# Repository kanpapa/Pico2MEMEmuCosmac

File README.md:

# Pico2MEMEmuCOSMAC

このリポジトリはkyo-ta04(DragonballEZ)さんの[Pico2ROMEmuBR](https://github.com/kyo-ta04/Pico2ROMEmuBR)のコードを応用して、COSMAC（CDP1802）のROM/RAMエミュレータとして動かしてみた実験的なプロジェクトです。

## 概要
- COSMAC CPUの動作クロックは1.79MHzです。
- ROM/RAMは各32KBを割り当てて確認しましたが、64KBのアドレス空間内であればカスタマイズ可能です。
- ROMにはテストプログラムとしてQ出力のLチカを組み込んでいます。rom_const.cのコメントを参照してください。
- 専用基板Rev.0.1にはSBC1802にあるインジケーターをオプション回路として追加しています。

詳細はソースをご確認ください。

## 回路図
- ブレッドボード版回路図

- 専用基板Rev.0.1 回路図

[PDF](/IMG/Pico2MEMEmuCosmac_sch_rev01.pdf)

## PCB
- [KiCADデータ](/kicad)
- [Gerberデータ](/kicad/gerber/)
- PCB 3Dイメージ

## BOM
|Item|Qty|Reference(s)|Value|Description|Datasheet|
| --- | --- | --- | --- | --- | --- |
|1|1|A1|RaspberryPi_Pico2|Raspberry Pi Pico 2|https://akizukidenshi.com/catalog/g/g129604/|
|2|1|U1|CDP1802ACE|CDP1802ACE microprocessor|http://www.cosmacelf.com/publications/data-sheets/cdp1802.pdf|
|3|1|C1|0.1uF|リード型積層セラミックコンデンサー 0.1μF50V F 2.54mm|https://akizukidenshi.com/catalog/g/g100090/|
|4|1|D1|1N4148|汎用小信号高速スイッチング・ダイオード 1N4148 100V200mA|https://akizukidenshi.com/catalog/g/g100941/|
|5|1|R1|100|カーボン抵抗(炭素皮膜抵抗) 1/6W100Ω|https://akizukidenshi.com/catalog/g/g116101/|
|6|2|RN1,RN2|10K|集合抵抗 4素子 10kΩ|https://akizukidenshi.com/catalog/g/g111909/|
|7|1|SW1|RUN|タクトスイッチ(水色)|https://akizukidenshi.com/catalog/g/g103649/|
|8|1|U1 socket||丸ピンICソケット (40P)|https://akizukidenshi.com/catalog/g/g100034/|
|9※|1|J1|Conn_01x06|ピンヘッダー (L型) 1×6 (6P)|https://akizukidenshi.com/catalog/g/g105336/|
|10※|1|U2|74HC04|6回路入インバーター TC74HC04AF|https://akizukidenshi.com/catalog/g/g111490/|
|11※|5|D2,D3,D4,D5,D6|LED|緑色チップLED 1608 OSG50603C1E|https://akizukidenshi.com/catalog/g/g108275/|
|12※|5|R2,R3,R4,R5,R6|1k|チップ抵抗 1608 1/8W1kΩ|https://akizukidenshi.com/catalog/g/g130351/|

※9～12はオプションです。

## マニュアル
- [Visual Studio Code での Raspberry Pi Pico プロジェクトのビルド方法](/docs/raspberry-pi-pico-vscode-build.md)
- [Lチカの楽しみかた](/docs/blink.md)
- [RCA BASIC3の楽しみかた](/docs/MCBASIC3.md)
- [MCSMP Super Monitor+BASIC3の楽しみかた](/docs/MCSMP20A.md)

## 資料
- ブレッドボードで実験中の様子

- 専用基板に実装した状態

- 専用基板で動作中の様子

## ライセンス
本プロジェクトのソースコードは[Pico2ROMEmuBR](https://github.com/kyo-ta04/Pico2ROMEmuBR)のライセンスに従います。

## 免責事項
本ソフトウェアは現状のまま提供されます。いかなる損害についても作者は責任を負いません。

## 謝辞
kyo-ta04(DragonballEZ)さんをはじめとするPico2ROMEmuプロジェクトに関わる全ての方々

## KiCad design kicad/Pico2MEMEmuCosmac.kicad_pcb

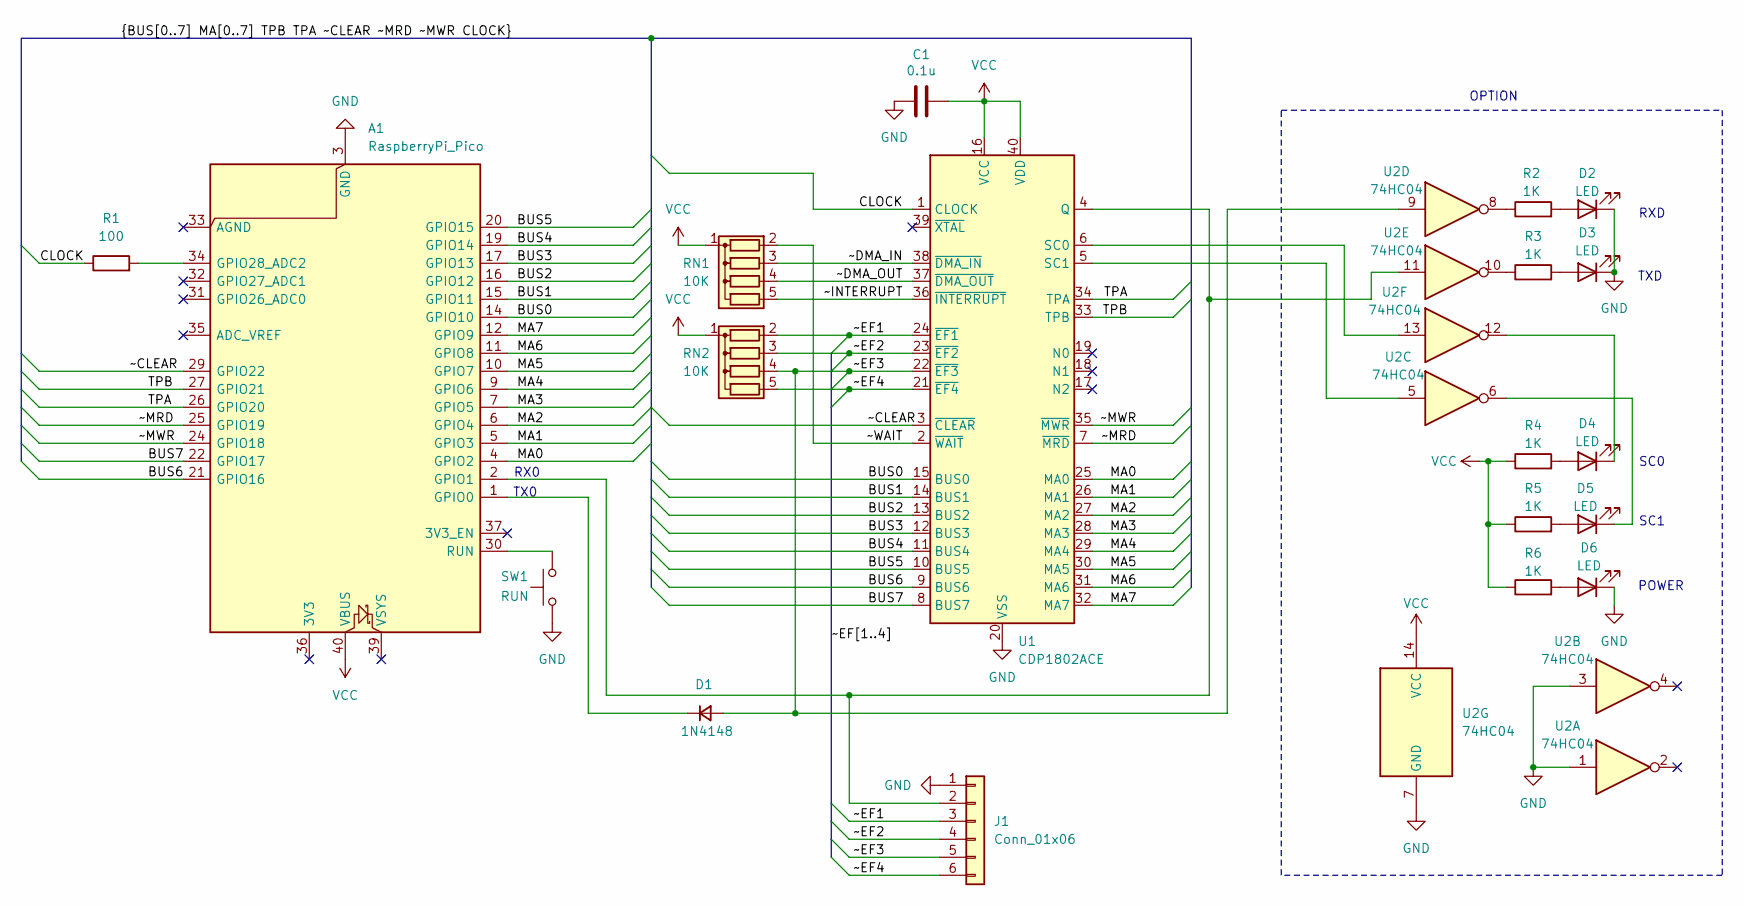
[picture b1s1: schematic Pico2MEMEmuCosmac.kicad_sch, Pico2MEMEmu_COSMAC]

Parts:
A1: RaspberryPi_Pico; RaspberryPi_Pico_Common_Unspecified
C1: 0.1u; C_Disc_D3.0mm_W1.6mm_P2.50mm
D1: 1N4148; D_DO-35_SOD27_P2.54mm_Vertical_KathodeUp
D2, D3, D4, D5, D6: LED; LED_0603_1608Metric
J1: Conn_01x06; PinHeader_1x06_P2.54mm_Vertical
R1: 100; R_Axial_DIN0204_L3.6mm_D1.6mm_P5.08mm_Horizontal
R2, R3, R4, R5, R6: 1K; R_0603_1608Metric
RN1, RN2: 10K; R_Array_SIP5
SW1: RUN; SW_PUSH_6mm
U1: CDP1802ACE; DIP-40_W15.24mm_Socket_LongPads
U2: 74HC04; SO-14_5.3x10.2mm_P1.27mm

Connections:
/BUS0: A1.14 (GPIO10), U1.15 (BUS0)
/BUS1: A1.15 (GPIO11), U1.14 (BUS1)
/BUS2: A1.16 (GPIO12), U1.13 (BUS2)
/BUS3: A1.17 (GPIO13), U1.12 (BUS3)
/BUS4: A1.19 (GPIO14), U1.11 (BUS4)
/BUS5: A1.20 (GPIO15), U1.10 (BUS5)
/BUS6: A1.21 (GPIO16), U1.9 (BUS6)
/BUS7: A1.22 (GPIO17), U1.8 (BUS7)
/CLOCK: R1.1, U1.1 (CLOCK)
/MA0: A1.4 (GPIO2), U1.25 (MA0)
/MA1: A1.5 (GPIO3), U1.26 (MA1)
/MA2: A1.6 (GPIO4), U1.27 (MA2)
/MA3: A1.7 (GPIO5), U1.28 (MA3)
/MA4: A1.9 (GPIO6), U1.29 (MA4)
/MA5: A1.10 (GPIO7), U1.30 (MA5)
/MA6: A1.11 (GPIO8), U1.31 (MA6)
/MA7: A1.12 (GPIO9), U1.32 (MA7)
/TPA: A1.26 (GPIO20), U1.34 (TPA)
/TPB: A1.27 (GPIO21), U1.33 (TPB)
/~CLEAR: A1.29 (GPIO22), U1.3 (~CLEAR)
/~DMA_IN: RN1.3 (R2), U1.38 (~DMA_IN)
/~DMA_OUT: RN1.4 (R3), U1.37 (~DMA_OUT)
/~EF1: J1.3, RN2.2 (R1), U1.24 (~EF1)
/~EF2: J1.4, RN2.3 (R2), U1.23 (~EF2)
/~EF3: D1.2 (A), J1.5, RN2.4 (R3), U1.22 (~EF3), U2.9
/~EF4: J1.6, RN2.5 (R4), U1.21 (~EF4)
/~INTERRUPT: RN1.5 (R4), U1.36 (~INTERRUPT)
/~MRD: A1.25 (GPIO19), U1.7 (~MRD)
/~MWR: A1.24 (GPIO18), U1.35 (~MWR)
/~WAIT: RN1.2 (R1), U1.2 (~WAIT)
GND: A1.3 (GND), A1.8 (GND), A1.13 (GND), A1.18 (GND), A1.23 (GND), A1.28 (GND), A1.38 (GND), C1.2, D2.1 (K), D3.1 (K), D6.1 (K), J1.1, SW1.2, U1.20 (VSS), U2.1, U2.3, U2.7 (GND)
unnamed: A1.1 (GPIO0), D1.1 (K)
unnamed: A1.2 (GPIO1), J1.2, U1.4 (Q), U2.11
unnamed: A1.34 (GPIO28_ADC2), R1.2
unnamed: A1.30 (RUN), SW1.1
unnamed: D2.2 (A), R2.2
unnamed: D3.2 (A), R3.2
unnamed: D4.2 (A), R4.2
unnamed: D4.1 (K), U2.12
unnamed: D5.2 (A), R5.2
unnamed: D5.1 (K), U2.6
unnamed: D6.2 (A), R6.2
unnamed: R2.1, U2.8
unnamed: R3.1, U2.10
unnamed: U1.6 (SC0), U2.13
unnamed: U1.5 (SC1), U2.5
VCC: A1.40 (VBUS), C1.1, R4.1, R5.1, R6.1, RN1.1 (common), RN2.1 (common), U1.16 (VCC), U1.40 (VDD), U2.14 (VCC)

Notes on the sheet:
SC1
RX0
TXD
TX0
OPTION
POWER
RXD
SC0

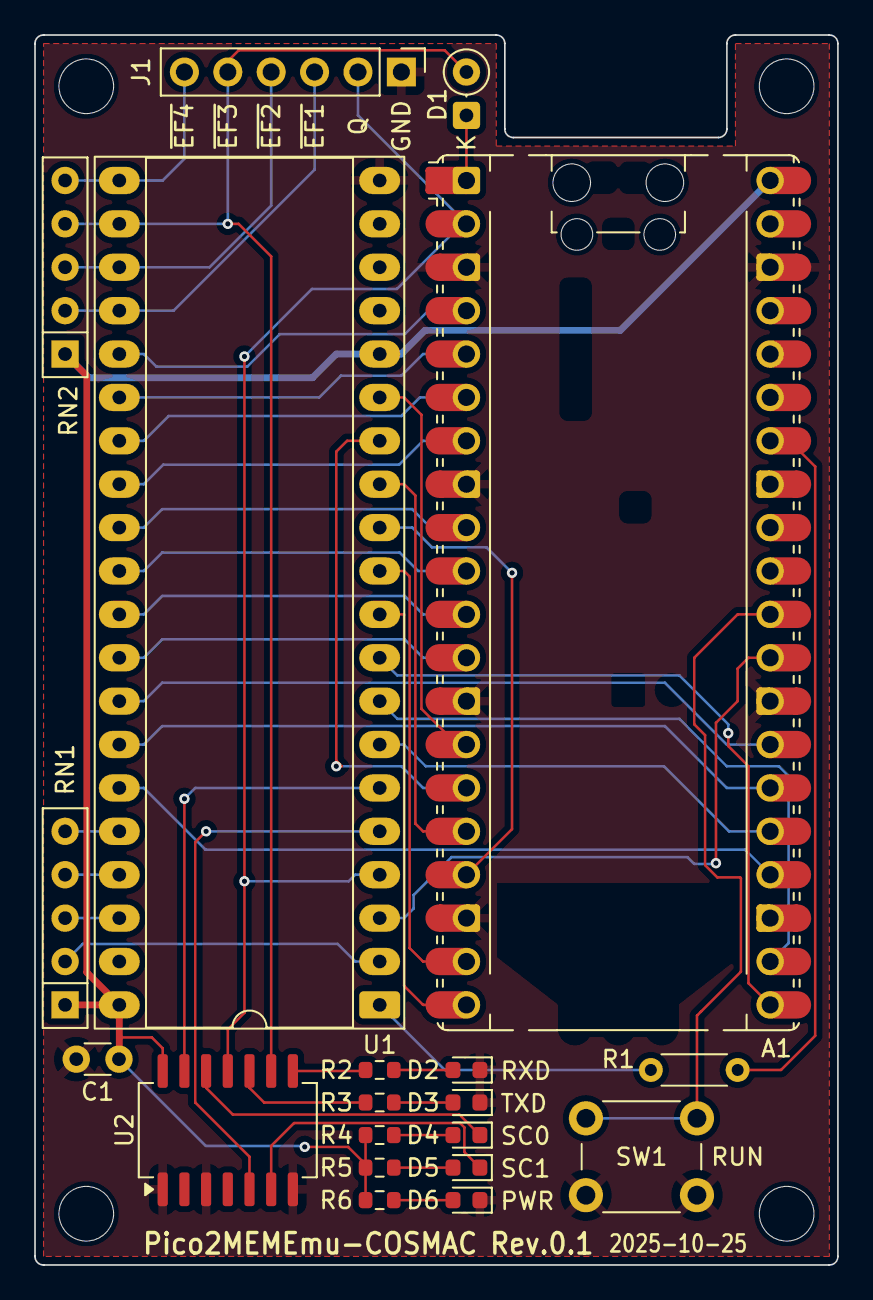
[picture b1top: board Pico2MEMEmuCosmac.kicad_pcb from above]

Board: 2 copper layers, 47.0 x 72.0 mm, 24 parts (0 on the bottom side), 47 nets.

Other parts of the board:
MH1, MH2, MH3, MH4: MountingHole_3.2mm_M3

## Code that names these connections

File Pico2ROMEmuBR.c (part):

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
#define DATA_PINS_BASE 10  // GP10～GP17 (D0-D7 8bit)
#define ADDR_PINS_BASE 2   // GP2～GP9 (MA0-MA7 8bit)
#define MWR_PIN 18
#define MRD_PIN 19
#define TPA_PIN 20
#define TPB_PIN 21
#define RESETOUT_PIN 22     // GP22 (リセット出力)
#define CLKOUT_PIN 28       // GP28 (クロック出力)

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
    // UART0の初期化
    uart_init(UART_ID, BAUD_RATE);
    // UARTピンの設定（GPIO0=TX, GPIO1=RX）
    gpio_set_function(UART_TX_PIN, GPIO_FUNC_UART);
    gpio_set_function(UART_RX_PIN, GPIO_FUNC_UART);

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    pio_sm_config c_addr = cdp1802_get_address_program_get_default_config(offset_addr);
    sm_config_set_in_pins(&c_addr, ADDR_PINS_BASE);
    sm_config_set_out_pins(&c_addr, DATA_PINS_BASE, 8);
    sm_config_set_jmp_pin(&c_addr, MRD_PIN); // MRDをJMPピンとして設定
    // PIOが制御するピンの方向を設定
    pio_sm_set_consecutive_pindirs(pio, sm_addr, ADDR_PINS_BASE, 8, false); // ADDRESSバスは入力
    pio_sm_set_consecutive_pindirs(pio, sm_addr, TPA_PIN, 1, false);  // TPAは入力
    pio_sm_set_consecutive_pindirs(pio, sm_addr, TPB_PIN, 1, false);  // TPBは入力
    pio_sm_set_consecutive_pindirs(pio, sm_addr, DATA_PINS_BASE, 8, false); // 初期は入力
    pio_sm_set_consecutive_pindirs(pio, sm_addr, MRD_PIN, 1, false);  // MRDは入力
    
    // 1. 書き込み用SM (sm_write)
    pio_sm_config c_write = cdp1802_write_mem_program_get_default_config(offset_write);
    sm_config_set_in_pins(&c_write, DATA_PINS_BASE); // DATAバスは入力
    // PIOが制御するピンの方向を設定
    pio_sm_set_consecutive_pindirs(pio, sm_write, MWR_PIN, 1, false); // MWR_PINは入力
    pio_sm_set_consecutive_pindirs(pio, sm_write, DATA_PINS_BASE, 8, false); // DATAバスは入力

    // 2. CPUクロック生成用SM (sm_clock)
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    }
    
    pio_gpio_init(pio, RESETOUT_PIN); // リセット出力ピン(GP25)の初期化
    pio_gpio_init(pio, MRD_PIN); // MRDピン(GP18)の初期化
    pio_gpio_init(pio, MWR_PIN); // MWRピン(GP19)の初期化
    pio_gpio_init(pio, TPA_PIN); // TPAピン(GP20)の初期化
    pio_gpio_init(pio, TPB_PIN); // TPBピン(GP21)の初期化
    pio_gpio_init(pio, CLKOUT_PIN); // CLK出力ピン(GP28)の初期化

    // Pullup
    gpio_set_pulls(MRD_PIN, true, false);
    gpio_set_pulls(MWR_PIN, true, false);

    // シフトレジスタの設定
    sm_config_set_in_shift(&c_write, false, false, 0); // ISR（入力シフトレジスタ）は左シフト方向
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
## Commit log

2025-10-12 Test for COSMAC
2025-10-12 TPAを実装
2025-10-12 ROMデータのコメントを修正
2025-10-12 コメントのアセンブリリストのLBRのコードを修正
2025-10-12 DATA BUSとADDRESS BUSを入れ替えた
2025-10-13 MWRとMRDのGPIOを入れ替えた。上位アドレスラッチはMRDではなくTPAのたち下がりに修正。
2025-10-13 不要なコメントを削除
2025-10-13 READMEと回路図を追加
2025-10-13 README_COSMACの文面を修正
2025-10-13 README_COSMACの体裁を調整
2025-10-13 README_COSMACの文章を修正
2025-10-13 README_COSMACに概要を追記
2025-10-13 MRDのチェックが漏れていたので追加
2025-10-16 MWRの実験的な実装
2025-10-16 IDIOTモニタをROMに入れて動作した
2025-10-17 不要なコードの削除とCPUクロック表示の修正
2025-10-17 バイナリからソースコードに変換するツールを追加
2025-10-17 回路図にシリアル通信を追加
2025-10-26 COSMACに特化した機能のため、Pico2ROMEmuBRからリポジトリを分離しました。
2025-10-26 リポジトリ分離に合わせてREADMEを見直し
2025-10-26 Kicadデータを追加
2025-10-26 3D Viewの画像を追加
2025-10-26 Rev.0.1基板の回路図を追加
2025-11-02 Rev.0.1基板のガーバーデータを追加
2025-11-03 BOMの追加とガーバーデータのリンクを追加
2025-11-03 回路図のPDFをリンク
2025-11-03 MCBASIC3の組み込み方法を追加
2025-11-03 RCA BASIC3の組み込みかたのリンクを追加
2025-11-03 MCSMP20Aの組み込みかたを追加
2025-11-03 MCSMP20Aのスクリーンショットを追加
2025-11-03 Blinkプログラムを整理し、IDIOTモニタを削除
2025-11-03 不要なコメントの削除
2025-11-03 メモリ設定をパターンで分けた
2025-11-04 Lチカの説明と各種写真の追加
2025-11-04 ファイル名の誤りを修正
2026-03-18 VSCode設定の修正
2026-03-18 サンプルとしてblinkのuf2ファイルを追加
2026-03-19 ファームウェアのビルド方法を補足
2026-03-19 ファイル名の変更等大幅に見直し
2026-03-19 VSCodeでのビルド方法を追記
2026-03-19 パスを修正
2026-03-19 blinkのサンプルuf2を登録
2026-03-19 blink1.asmのアセンブルリストを追加
2026-03-19 キャプチャを追加
2026-03-19 キャプチャの配置を修正
2026-03-19 コメントを修正
